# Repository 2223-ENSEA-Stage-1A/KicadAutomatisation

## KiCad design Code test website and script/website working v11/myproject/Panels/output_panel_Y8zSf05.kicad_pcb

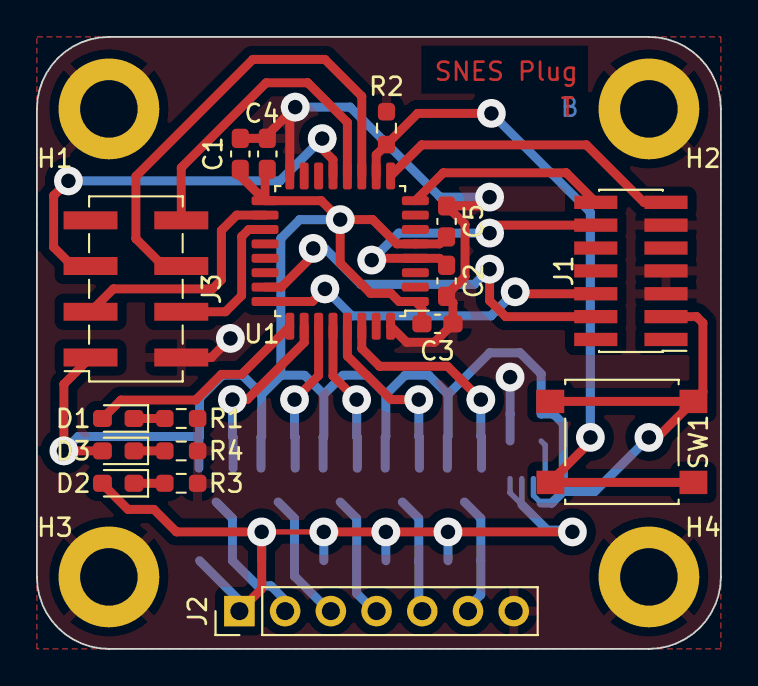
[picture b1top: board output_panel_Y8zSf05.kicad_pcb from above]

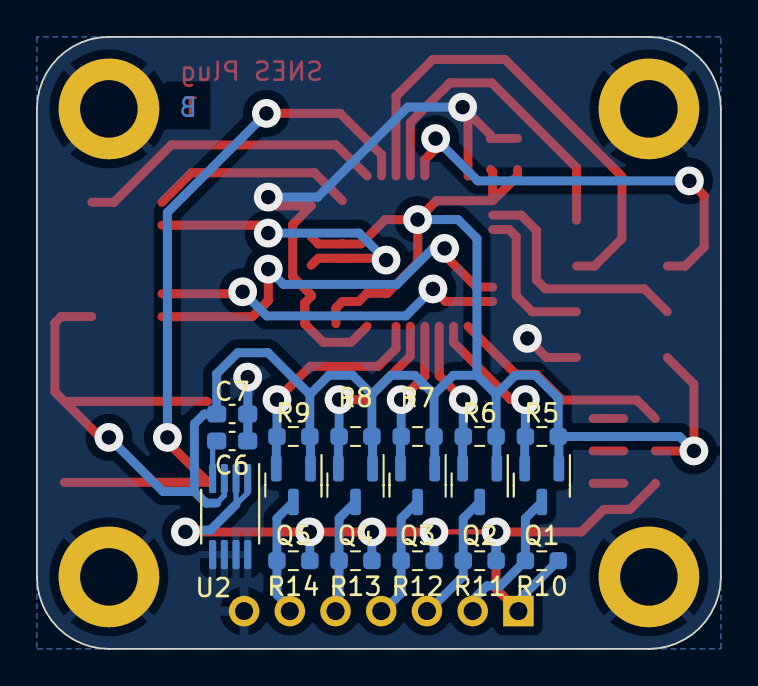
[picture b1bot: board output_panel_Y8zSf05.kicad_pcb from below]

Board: 2 copper layers, 38.0 x 34.0 mm, 39 parts (18 on the bottom side), 29 nets.

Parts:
C1: 10u; C_0603_1608Metric_Pad1.08x0.95mm_HandSolder
C2, C3, C4, C5: 100n; C_0603_1608Metric_Pad1.08x0.95mm_HandSolder
C6: 470p; C_0603_1608Metric_Pad1.08x0.95mm_HandSolder
C7: 2.2u; C_0603_1608Metric_Pad1.08x0.95mm_HandSolder
D1, D2: LED_Small; D_0603_1608Metric_Pad1.05x0.95mm_HandSolder
D3: LED; D_0603_1608Metric_Pad1.05x0.95mm_HandSolder
H1, H2, H3, H4: MountingHole_Pad; MountingHole_3.2mm_M3_DIN965_Pad
J1: Conn_02x07_Odd_Even; PinHeader_2x07_P1.27mm_Vertical_SMD
J2: Conn_01x07_Socket; PinHeader_1x07_P2.54mm_Vertical
J3: Conn_01x08_Socket; PinSocket_2x04_P2.54mm_Vertical_SMD
Q1, Q2, Q3, Q4, Q5: 2N7002; SOT-23
R1, R3, R4: 1k; R_0603_1608Metric_Pad0.98x0.95mm_HandSolder
R2, R5, R6, R7, R8, R9, R10, R11, R12, R13, R14: 10k; R_0603_1608Metric_Pad0.98x0.95mm_HandSolder
SW1: SW_SPST; SW_SPST_B3S-1000
U1: STM32L412KBTx; LQFP-32_7x7mm_P0.8mm
U2: MIC5219-3.3YMM; MSOP-8_3x3mm_P0.65mm

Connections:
+3.3V-v0-: C1.1, C3.1, C4.1, C5.1, C7.1, D3.2 (A), J1.3, J3.1, Q1.1 (G), Q2.1 (G), Q3.1 (G), Q4.1 (G), Q5.1 (G), R5.1, R6.1, R7.1, R8.1, R9.1, SW1.2 (B), U1.1 (VDD), U1.5 (VDDA), U1.17 (VDD), U2.3 (OUT)
+5V-v0-: D2.2 (A), J2.1, R10.1, R11.1, R12.1, R13.1, R14.1, U2.1 (EN), U2.2 (IN)
Appairing_Btn-v0-: R2.1, SW1.1 (A), U1.10 (PA4)
Chip_Enable-v0-: J3.4, U1.19 (PA9)
Data_Clock_SNES-v0-: J2.2, Q1.3 (D), R10.2
Data_Clock_STM32-v0-: Q1.2 (S), R5.2, U1.26 (PB3)
Data_Latch_SNES-v0-: J2.3, Q2.3 (D), R11.2
Data_Latch_STM32-v0-: Q2.2 (S), R6.2, U1.27 (PB4)
GND-v0-: C1.2, C2.1, C3.2, C4.2, C5.2, C6.2, C7.2, H1.1, H2.1, H3.1, H4.1, J1.5, J1.7, J1.11, J2.7, J3.2, R1.2, R2.2, R3.2, R4.2, U1.16 (VSS), U1.32 (VSS), U2.5 (GND-v0-), U2.6 (GND-v0-), U2.7 (GND-v0-), U2.8 (GND-v0-)
IOBit_SNES-v0-: J2.6, Q5.3 (D), R14.2
IOBit_STM32-v0-: Q5.2 (S), R9.2, U1.30 (PB7)
NRST-v0-: C2.2, J1.12, U1.4 (NRST-v0-)
unnamed: D1.1 (K), R1.1
unnamed: D2.1 (K), R3.1
unnamed: D3.1 (K), R4.1
unnamed: C6.1, U2.4 (BP)
SPI_Chip_Select-v0-: J3.3, U1.18 (PA8)
SPI_Clock-v0-: J3.6, U1.11 (PA5)
SPI_Digital_Input-v0-: J3.8, U1.12 (PA6)
SPI_Digital_Output-v0-: J3.5, U1.13 (PA7)
SWDCK-v0-: J1.6, U1.24 (PA14)
SWDIO-v0-: J1.4, U1.23 (PA13)
Serial_Data1_SNES-v0-: J2.4, Q3.3 (D), R12.2
Serial_Data1_STM32-v0-: Q3.2 (S), R7.2, U1.28 (PB5)
Serial_Data2_SNES-v0-: J2.5, Q4.3 (D), R13.2
Serial_Data2_STM32-v0-: Q4.2 (S), R8.2, U1.29 (PB6)
Status_LED-v0-: D1.2 (A), U1.25 (PA15)
USART2_RX-v0-: J1.13, U1.9 (PA3)
USART2_TX-v0-: J1.14, U1.8 (PA2)

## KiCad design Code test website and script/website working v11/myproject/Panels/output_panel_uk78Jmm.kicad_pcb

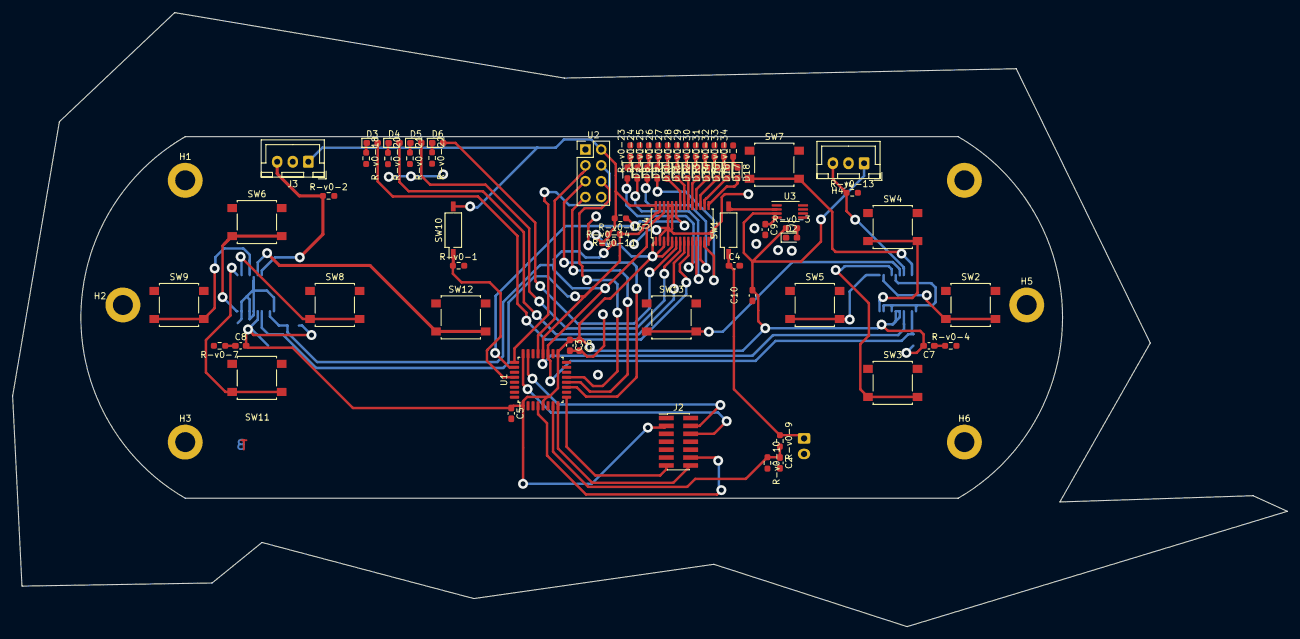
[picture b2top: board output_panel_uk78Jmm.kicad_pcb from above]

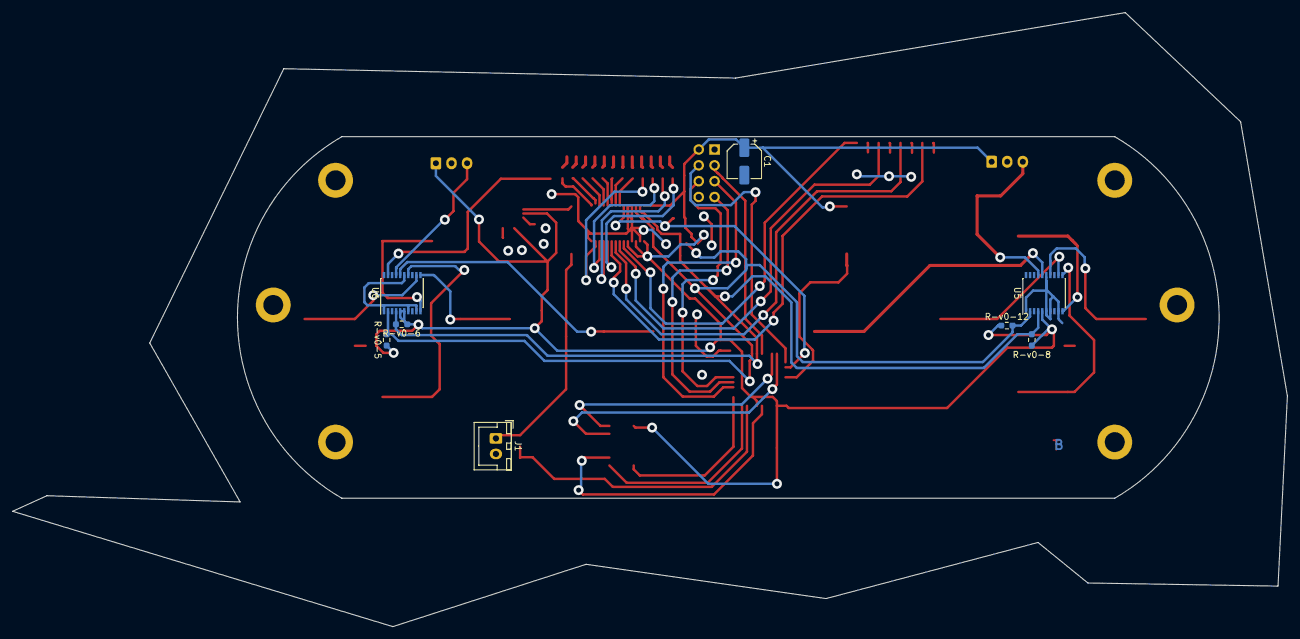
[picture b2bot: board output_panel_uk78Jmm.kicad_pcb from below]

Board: 2 copper layers, 204.5 x 98.5 mm, 87 parts (8 on the bottom side), 68 nets.

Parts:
C1: 22uF; CP_Elec_5x5.4
C2: 1nF; C_0603_1608Metric_Pad1.08x0.95mm_HandSolder
C3, C5: 100n; C_0603_1608Metric_Pad1.08x0.95mm_HandSolder
C4: 1u; C_0603_1608Metric_Pad1.08x0.95mm_HandSolder
C6: 10u; C_0603_1608Metric_Pad1.08x0.95mm_HandSolder
C7, C8, C10: 100nF; C_0603_1608Metric_Pad1.08x0.95mm_HandSolder
C9: 470p; C_0603_1608Metric_Pad1.08x0.95mm_HandSolder
D2: L-v0-ED_Small; L-v0-ED_0603_1608Metric_Pad1.05x0.95mm_HandSolder
D3: G1; L-v0-ED_0603_1608Metric_Pad1.05x0.95mm_HandSolder
D4: G2; L-v0-ED_0603_1608Metric_Pad1.05x0.95mm_HandSolder
D5: G3; L-v0-ED_0603_1608Metric_Pad1.05x0.95mm_HandSolder
D6: G4; L-v0-ED_0603_1608Metric_Pad1.05x0.95mm_HandSolder
D7: G5; L-v0-ED_0603_1608Metric_Pad1.05x0.95mm_HandSolder
D8: G6; L-v0-ED_0603_1608Metric_Pad1.05x0.95mm_HandSolder
D9: G7; L-v0-ED_0603_1608Metric_Pad1.05x0.95mm_HandSolder
D10: G8; L-v0-ED_0603_1608Metric_Pad1.05x0.95mm_HandSolder
D11: O1; L-v0-ED_0603_1608Metric_Pad1.05x0.95mm_HandSolder
D12: O2; L-v0-ED_0603_1608Metric_Pad1.05x0.95mm_HandSolder
D13: O3; L-v0-ED_0603_1608Metric_Pad1.05x0.95mm_HandSolder
D14: O4; L-v0-ED_0603_1608Metric_Pad1.05x0.95mm_HandSolder
D15: R-v0-1; L-v0-ED_0603_1608Metric_Pad1.05x0.95mm_HandSolder
D16: R-v0-2; L-v0-ED_0603_1608Metric_Pad1.05x0.95mm_HandSolder
D17: R-v0-3; L-v0-ED_0603_1608Metric_Pad1.05x0.95mm_HandSolder
D18: R-v0-4; L-v0-ED_0603_1608Metric_Pad1.05x0.95mm_HandSolder
H1, H2, H3, H4, H5, H6: MountingHole_Pad; MountingHole_3.2mm_M3_DIN965_Pad
J1: Conn_01x02; JST_XH_B2B-XH-A_1x02_P2.50mm_Vertical
J2: Conn_02x07_Odd_Even; PinHeader_2x07_P1.27mm_Vertical_SMD
J3, J4: Conn_01x03; JST_XH_B3B-XH-A_1x03_P2.50mm_Vertical
R-v0-1, R-v0-2, R-v0-3, R-v0-13, R-v0-18, R-v0-20, R-v0-21, R-v0-22, R-v0-23, R-v0-24, R-v0-25, R-v0-26, R-v0-27, R-v0-28, R-v0-29, R-v0-30, R-v0-31, R-v0-32, R-v0-33, R-v0-34: 1K; R-v0-_0603_1608Metric_Pad0.98x0.95mm_HandSolder
R-v0-4, R-v0-7: 1k; R-v0-_0603_1608Metric_Pad0.98x0.95mm_HandSolder
R-v0-5, R-v0-6, R-v0-8, R-v0-11, R-v0-12, R-v0-14, R-v0-16: 10K; R-v0-_0603_1608Metric_Pad0.98x0.95mm_HandSolder
R-v0-9, R-v0-10: 1M; R-v0-_0603_1608Metric_Pad0.98x0.95mm_HandSolder
SW1, SW10: SW_DIP_x01; SW_DIP_SPSTx01_Slide_Copal_CHS-01B_W7.62mm_P1.27mm
SW2, SW3, SW4, SW5, SW6, SW8, SW9, SW11, SW12, SW13: SW_Push; SW_SPST_B3S-1000
SW7: SW_SPST; SW_SPST_B3S-1000
U1: STM32L-v0-412KBTx; L-v0-QFP-32_7x7mm_P0.8mm
U2: nR-v0-F24_Full; PinHeader_2x04_P2.54mm_Vertical
U3: MIC5219-3.3YMM; MSOP-8_3x3mm_P0.65mm
U4: PCA9685PW; TSSOP-28_4.4x9.7mm_P0.65mm
U5, U6: PCF8574TS; SSOP-20_4.4x6.5mm_P0.65mm

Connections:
A_Button-v0-: SW2.2, U6.12 (P2)
B_Button-v0-: SW3.2, U6.14 (P3)
CSN_nR-v0-F24: U1.25 (PA15), U2.4 (CSN)
DC_Button-v0-: SW11.2, U5.11 (P1)
DIODE_OE-v0-: R-v0-16.1, U1.26 (PB3), U4.23 (~OE)
DIO/EX_CL-v0-K: R-v0-5.2, R-v0-12.2, R-v0-14.2, U1.19 (PA9), U4.26 (SCL-v0-), U5.2 (SCL-v0-), U6.2 (SCL-v0-)
DIO/EX_SDA-v0-: R-v0-6.2, R-v0-8.2, R-v0-11.1, U1.20 (PA10), U4.27 (SDA), U5.4 (SDA), U6.4 (SDA)
Digital_Out_Put-v0-: U1.12 (PA6), U2.7 (MISO)
GND-v0-: C1.2, C2.2, C3.2, C4.2, C5.2, C6.2, C9.2, C10.2, D2.1 (K), H1.1, H2.1, H3.1, H4.1, H5.1, H6.1, J1.2, J2.5, J2.7, J2.11, J3.2, J4.2, R-v0-1.2, R-v0-2.2, R-v0-4.2, R-v0-7.2, R-v0-10.2, R-v0-13.2, R-v0-18.2, R-v0-20.2, R-v0-21.2, R-v0-22.2, R-v0-23.2, R-v0-24.2, R-v0-25.2, R-v0-26.2, R-v0-27.2, R-v0-28.2, R-v0-29.2, R-v0-30.2, R-v0-31.2, R-v0-32.2, R-v0-33.2, R-v0-34.2, SW2.1, SW3.1, SW4.1, SW5.1, SW6.1, SW7.1 (A), SW8.1, SW9.1, SW11.1, SW12.1, SW13.1, U1.16 (VSS), U1.32 (VSS), U2.1 (GND-v0-), U3.5 (GND-v0-), U3.6 (GND-v0-), U3.7 (GND-v0-), U3.8 (GND-v0-), U4.2 (A1), U4.4 (A3), U4.14 (VSS), U4.24 (A5), U4.25 (EXTCL-v0-K), U5.1 (~INT), U5.6 (A0), U5.7 (A1), U5.9 (A2), U5.15 (VSS), U6.1 (~INT), U6.7 (A1), U6.9 (A2), U6.15 (VSS)
Glob_Alim-v0-: C1.1, C3.1, C5.1, C6.1, C7.2, C8.2, C10.1, J2.3, J3.1, J4.1, R-v0-3.1, R-v0-5.1, R-v0-6.1, R-v0-8.1, R-v0-11.2, R-v0-12.1, R-v0-14.1, R-v0-16.2, SW10.2, U1.1 (VDD), U1.5 (VDDA), U1.17 (VDD), U2.2 (VCC), U3.3 (OUT), U4.1 (A0), U4.3 (A2), U4.5 (A4), U4.28 (VDD), U5.5 (VDD), U6.5 (VDD), U6.6 (A0)
L-v0-: J4.3, R-v0-13.1, U6.17 (P5)
L-v0-C_Button: SW8.2, U5.12 (P2)
L-v0-i-ion-v0-: C4.1, J1.1, R-v0-9.1, SW1.1
MOSI-v0-: U1.13 (PA7), U2.6 (MOSI-v0-)
NES/SNES_switcher-v0-: R-v0-1.1, SW10.1, U1.28 (PB5)
unnamed: SW1.2, U3.2 (IN)
unnamed: C7.1, R-v0-4.1
unnamed: C8.1, R-v0-7.1
unnamed: D2.2 (A), R-v0-3.2
unnamed: D3.2 (A), U4.9 (L-v0-ED3)
unnamed: D3.1 (K), R-v0-18.1
unnamed: D4.2 (A), U4.8 (L-v0-ED2)
unnamed: D4.1 (K), R-v0-20.1
unnamed: D5.2 (A), U4.7 (L-v0-ED1)
unnamed: D5.1 (K), R-v0-21.1
unnamed: D6.2 (A), U4.6 (L-v0-ED0)
unnamed: D6.1 (K), R-v0-22.1
unnamed: D7.2 (A), U4.10 (L-v0-ED4)
unnamed: D7.1 (K), R-v0-23.1
unnamed: D8.2 (A), U4.11 (L-v0-ED5)
unnamed: D8.1 (K), R-v0-24.1
unnamed: D9.2 (A), U4.12 (L-v0-ED6)
unnamed: D9.1 (K), R-v0-25.1
unnamed: D10.2 (A), U4.13 (L-v0-ED7)
unnamed: D10.1 (K), R-v0-26.1
unnamed: D11.2 (A), U4.22 (L-v0-ED15)
unnamed: D11.1 (K), R-v0-27.1
unnamed: D12.2 (A), U4.21 (L-v0-ED14)
unnamed: D12.1 (K), R-v0-28.1
unnamed: D13.2 (A), U4.20 (L-v0-ED13)
unnamed: D13.1 (K), R-v0-29.1
unnamed: D14.2 (A), U4.19 (L-v0-ED12)
unnamed: D14.1 (K), R-v0-30.1
unnamed: D15.2 (A), U4.18 (L-v0-ED11)
unnamed: D15.1 (K), R-v0-31.1
unnamed: D16.2 (A), U4.17 (L-v0-ED10)
unnamed: D16.1 (K), R-v0-32.1
unnamed: D17.2 (A), U4.16 (L-v0-ED9)
unnamed: D17.1 (K), R-v0-33.1
unnamed: D18.2 (A), U4.15 (L-v0-ED8)
unnamed: D18.1 (K), R-v0-34.1
unnamed: C9.1, U3.4 (BP)
Order_Search-v0-: SW7.2 (B), U6.19 (P6)
POWER-v0-_CHECK-v0-: C2.1, R-v0-9.2, R-v0-10.1, U1.7 (PA1)
Pin_Clock-v0-: U1.11 (PA5), U2.5 (SCK)
R-v0-: J3.3, R-v0-2.1, U5.17 (P5)
R-v0-C_Button: SW9.2, U5.14 (P3)
R-v0-X/TX: U1.21 (PA11), U2.3 (CE)
R-v0-eset_Buton -v0-: J2.12, U1.4 (NR-v0-ST)
SE_Button-v0-: SW13.2, U6.16 (P4)
ST_Button-v0-: SW12.2, U5.16 (P4)
SWDCK-v0-: J2.6, U1.24 (PA14)
SWDIO-v0-: J2.4, U1.23 (PA13)
UC_Button-v0-: SW6.2, U5.10 (P0)
USAR-v0-T2_R-v0-X-v0-: J2.13, U1.9 (PA3)
USAR-v0-T2_TX-v0-: J2.14, U1.8 (PA2)
X_Button-v0-: SW4.2, U6.10 (P0)
Y_Button-v0-: SW5.2, U6.11 (P1)
